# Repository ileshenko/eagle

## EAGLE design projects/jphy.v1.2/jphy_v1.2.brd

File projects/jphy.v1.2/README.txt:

Second bunch of the board (blue version) - 100 pcs.

Changes:
- Use 0805 devices instead of 1206;
- Use SMD LED and resistor;
- Change RJ45 drills from 2.54mm to 3mm.
- Change RJ45 ...

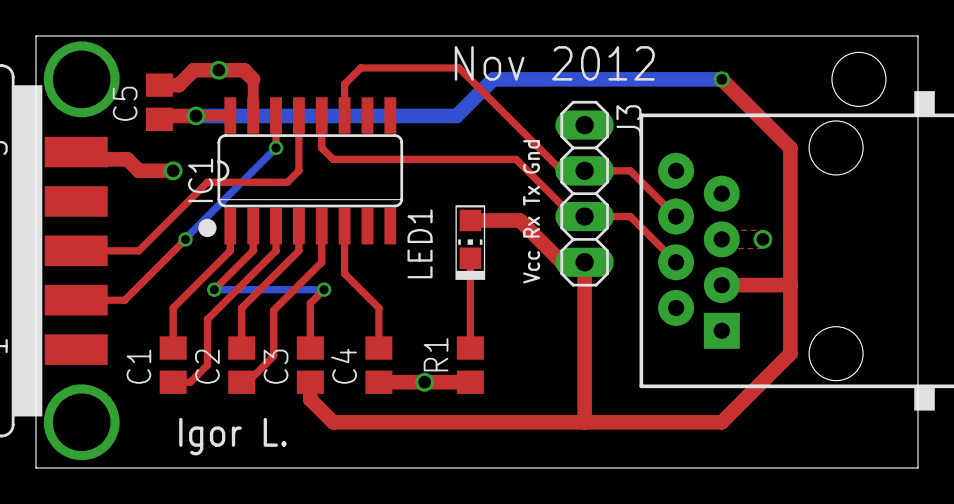
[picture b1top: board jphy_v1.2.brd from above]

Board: 2 copper layers, 49.0 x 24.0 mm, 11 parts (0 on the bottom side), 13 nets.

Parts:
C1, C2, C3, C4, C5: 0.47 uF; C0805
IC1: MAX3232ESE; SO16
J1: RJ45-8X; RJ45-NO-SHIELD
J2: F09D
J3: 1X04
LED1: Green; CHIP-LED0805
R1: 270 R; R0805

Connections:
GND: C4.1, C5.2, IC1.15, J1.5, J2.5, J3.1, R1.1
unnamed: LED1.C, R1.2
unnamed: C3.2, IC1.2
unnamed: C4.2, IC1.6
unnamed: C1.1, IC1.3
unnamed: C1.2, IC1.1
unnamed: C2.1, IC1.5
unnamed: C2.2, IC1.4
unnamed: IC1.14, J2.2
unnamed: IC1.13, J2.3
RX_TTL: IC1.12, J1.4, J3.3
TX_TTL: IC1.11, J1.6, J3.2
VCC: C3.1, C5.1, IC1.16, J1.3, J3.4, LED1.A

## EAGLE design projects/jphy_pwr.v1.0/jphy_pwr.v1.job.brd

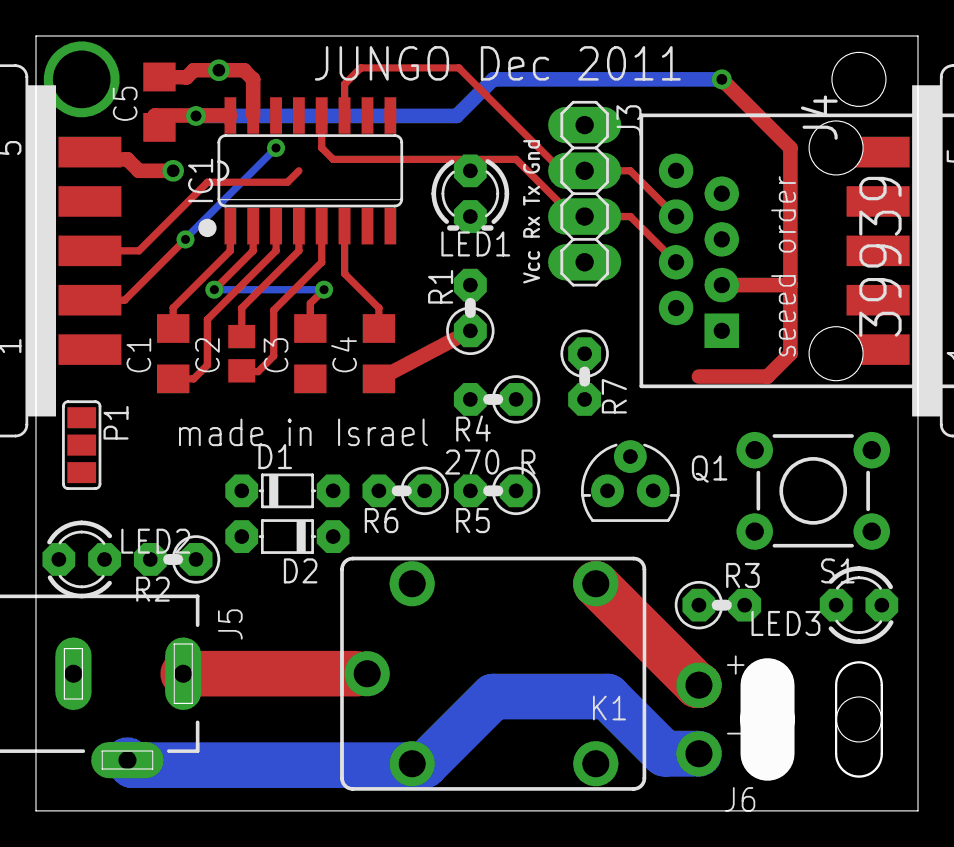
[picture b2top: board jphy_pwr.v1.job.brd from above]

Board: 2 copper layers, 49.0 x 43.0 mm, 28 parts (0 on the bottom side), 29 nets.

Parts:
C1, C3, C4, C5: 0.47 uF; C1206
C2: 0.47 uF; C0805
D1, D2: D-5
IC1: MAX3232ESE; SO16
J1: RJ45-8X; RJ45-NO-SHIELD
J2: F09D
J3: 1X04
J4: M09D
J5: DCJ0202
J6: FLEX-POWER
K1: CQ1-12V; CQ1
LED1: Green; LED3MM
LED2, LED3: Red; LED3MM
P1: 3P-SMD-4.8X2
Q1: TO-92-TRIANGLE
R1, R2, R3, R4, R5, R6, R7: 270 R; 0207/2V
S1: TACTILE-PTH

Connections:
12VOUT: J6.1, K1.NC, LED3.A
+12V: J5.1, K1.C, LED2.A, Q1.1, R7.2
CTS: J2.8, J4.8
DCD: J2.1, J4.1
DSR: J2.6, J4.6
DTR: J2.4, J4.4, P1.1
GND: C4.1, C5.2, D2.A, IC1.15, J1.5, J2.5, J3.1, J4.5, J5.2, J6.2, K1.2, R1.1, R2.1, R3.1, S1.1, S1.2
unnamed: LED1.K, R1.2
unnamed: C3.2, IC1.2
unnamed: C4.2, IC1.6
unnamed: C1.1, IC1.3
unnamed: C1.2, IC1.1
unnamed: C2.1, IC1.5
unnamed: C2.2, IC1.4
unnamed: LED2.K, R2.2
unnamed: LED3.K, R3.2
unnamed: D2.C, K1.1, Q1.3
unnamed: R4.1, S1.3, S1.4
unnamed: Q1.2, R5.1
unnamed: D1.A, R6.2
unnamed: R4.2, R5.2, R6.1, R7.1
PWR_MNG: D1.C, P1.2
RI: J2.9, J4.9
RTS: J2.7, J4.7, P1.3
RXD: IC1.14, J2.2, J4.2
RX_TTL: IC1.12, J1.4, J3.3
TXD: IC1.13, J2.3, J4.3
TX_TTL: IC1.11, J1.6, J3.2
VCC: C3.1, C5.1, IC1.16, J1.3, J3.4, LED1.A

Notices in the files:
parts and their libraries:
SparkFun: Licensing: CC v3.0 Share-Alike You are welcome to use this library for commercial purposes.
